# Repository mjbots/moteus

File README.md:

# moteus brushless servo #

This contains full designs for the moteus brushless servo actuator,
including firmware and PCBs.

**WARNING**: This is not just a software project.  It includes designs
for moderately high power electronics.  It has not yet burned down my
(or anyone's that I know of) house, but there are no guarantees.

# Specifications #

| Name                   | r4.11        | r5         | c1         | n1          | x1          |
|------------------------|--------------|------------|------------|-------------|-------------|
| Voltage Input          | 10-44V       | 10-34V     | 10-51V     | 10-54V      | 10-54V      |
| Peak Electrical Power  | 900W @ 30V   | 600W @ 26V | 250W @ 28V | 1.3kW @ 36V | 1kW @ 36V   |
| Mass                   | 14.2g        | 10.0g      | 8.9g       | 14.6g       | 23.8g       |
| Control Rate           | 15-30kHz     | -          | -          | -           | -           |
| PWM Switching Rate     | 15-60kHz     | -          | -          | -           | -           |
| CPU                    | STM32G4      | -          | -          | -           | -           |
| Uncooled phase current | 12A          | 15A        | 5A         | 9A          | 25A         |
| Cooled phase current   | 32A          | 42A        | 14A        | 26A         | 62A         |
| Peak phase current     | 100A         | 100A       | 20A        | 100A        | 120A        |
| Communications         | 5Mbps CAN-FD | -          | -          | -           | -           |
| Dimensions             | 46x53mm      | 40x40x9mm  | 38x38x9mm  | 46x46x8mm   | 56x56x10mm  |

Assembled and tested boards can be purchased at: https://mjbots.com

# Directory structure #

* hw/ - hardware (mechanical and electrical designs)
  * controller/ - PCB design for moteus-r4.11
  * c1/ - PCB design for moteus-c1
  * n1/ - PCB design for moteus-n1
  * x1/ - PCB design for moteus-x1
* fw/ - firmware for brushless controller
* lib/ - client side software
* utils/ - diagnostic tools
* tools/ - bazel build configure
* docs/ - documentation

# Documentation #

* [Quick Start](https://mjbots.github.io/moteus/quick-start)
* [All Documentation](https://mjbots.github.io/moteus/)
* [Discord](https://discord.gg/W4hUpBb)

# Misc #

 * 

# How to support moteus development #

The easiest way to support development the moteus hardware and firmware is as follows:

1) Buy things from https://mjbots.com
2) Build awesome machines!

That's it!  If for some reason you want to go above and beyond, you can sponsor mjbots through github: https://github.com/sponsors/mjbots

# License #

All files contained in this repository, unless otherwise noted, are
available under an Apache 2.0 License:
https://www.apache.org/licenses/LICENSE-2.0

# Trademark #

mjbots Robotic Systems LLC owns and protects the "mjbots" and "moteus" trademarks in many jurisdictions.

If you want to use these names in your project or product, please read the [Trademark Policy](https://mjbots.com/trademark-policy)

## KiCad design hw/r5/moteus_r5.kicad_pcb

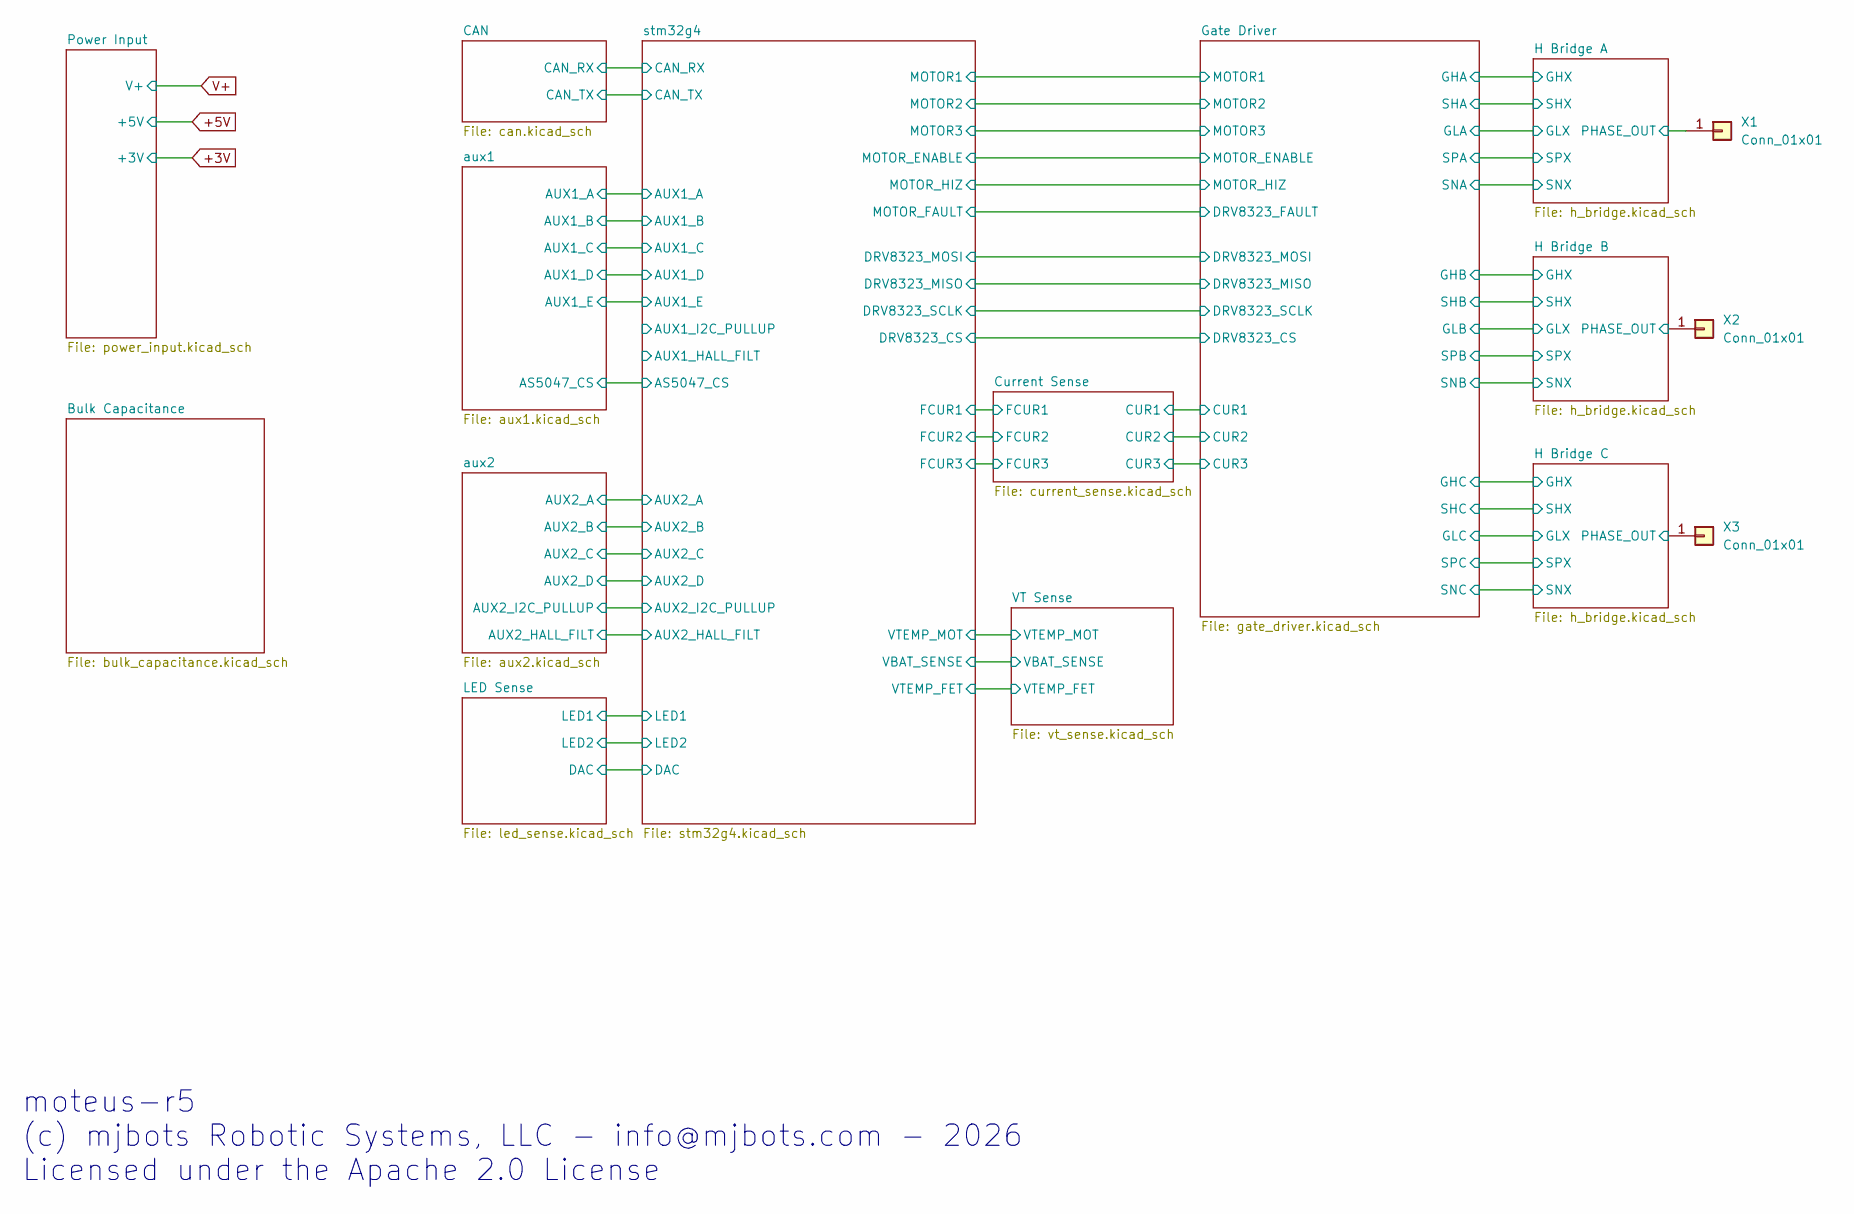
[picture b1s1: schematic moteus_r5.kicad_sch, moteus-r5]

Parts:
X1, X3: Conn_01x01; POWER_M2.5_EDGE
X2: Conn_01x01; POWER_M2.5

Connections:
/H Bridge A/OUTX: X1.1; also elsewhere on the board
/H Bridge B/OUTX: X2.1; also elsewhere on the board
/H Bridge C/OUTX: X3.1; also elsewhere on the board

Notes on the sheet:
moteus-r5 (c) mjbots Robotic Systems, LLC - info@mjbots.com - 2026 Licensed under the Apache 2.0 License

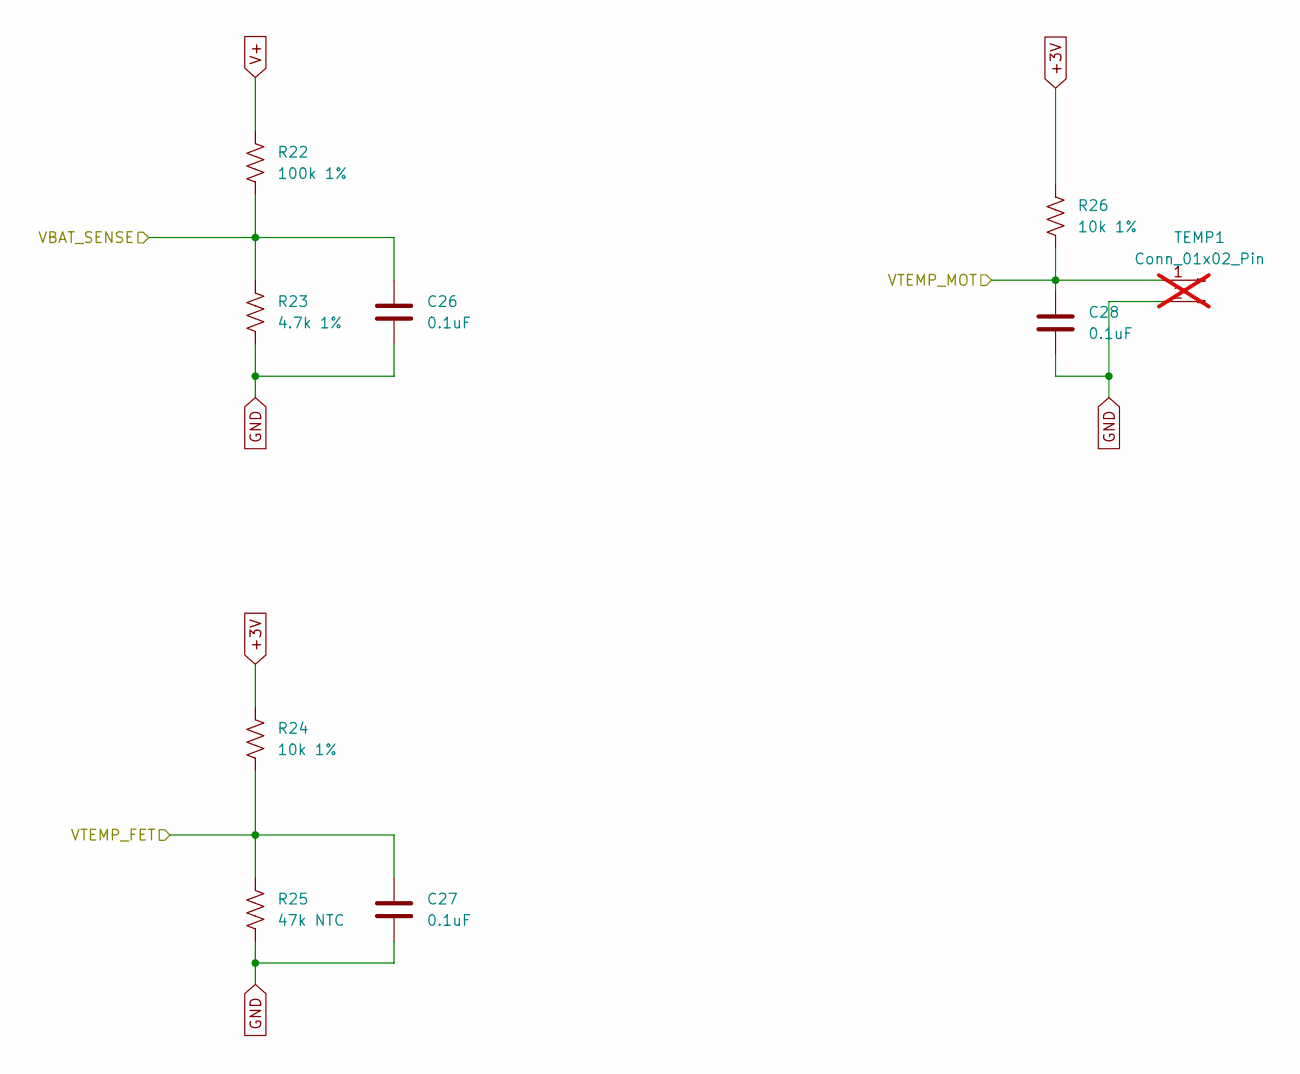
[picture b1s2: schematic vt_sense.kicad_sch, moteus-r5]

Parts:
C26, C27, C28: 0.1uF; C_0402_1005Metric; MPN MF-CAP-0402-0.1uF
R22: 100k 1%; R_0402_1005Metric; MPN RC0402FR-07100KL
R23: 4.7k 1%; R_0402_1005Metric; MPN RC0402FR-074K7L
R24, R26: 10k 1%; R_0402_1005Metric; MPN RC0402FR-0710KL
R25: 47k NTC; R_0402_1005Metric; MPN NCP15WB473F03RC
TEMP1: Conn_01x02_Pin; PinHeader_1x02_P2.00mm_Vertical; not fitted

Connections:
+3V: R24.1, R26.1; also elsewhere on the board
/VT Sense/VBAT_SENSE: C26.1, R22.2, R23.1; also elsewhere on the board
/VT Sense/VTEMP_FET: C27.1, R24.2, R25.1; also elsewhere on the board
/VT Sense/VTEMP_MOT: C28.1, R26.2, TEMP1.1; also elsewhere on the board
GND: C26.2, C27.2, C28.2, R23.2, R25.2, TEMP1.2; also elsewhere on the board
V+: R22.1; also elsewhere on the board

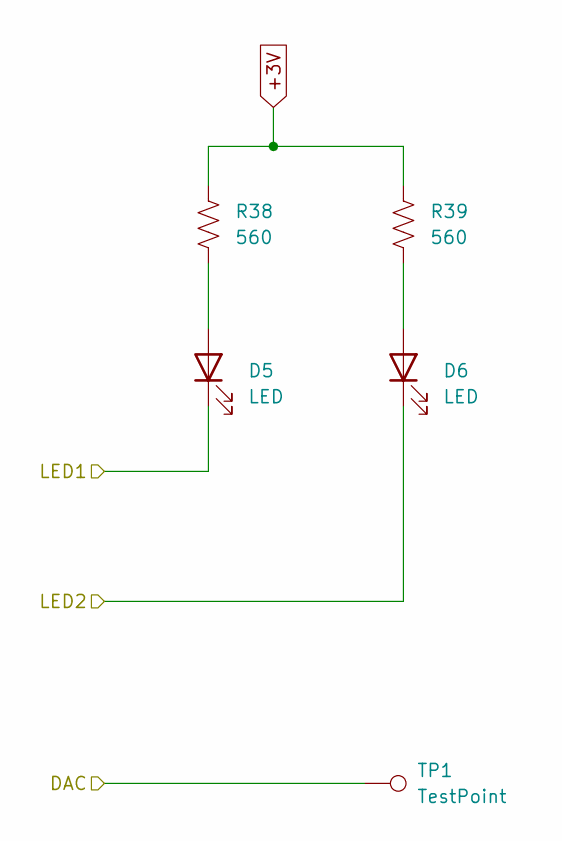
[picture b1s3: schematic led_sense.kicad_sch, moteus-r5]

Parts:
D5: LED; LED_0603_1608Metric; MPN MF-LED-0603-RED
D6: LED; LED_0603_1608Metric; MPN MF-LED-0603-GREEN
R38, R39: 560; R_0402_1005Metric; MPN MF-RES-0402-560
TP1: TestPoint; TestPoint_THTPad_D1.0mm_Drill0.5mm

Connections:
+3V: R38.1, R39.1; also elsewhere on the board
/LED Sense/DAC: TP1.1; also elsewhere on the board
/LED Sense/LED1: D5.1 (K); also elsewhere on the board
/LED Sense/LED2: D6.1 (K); also elsewhere on the board
unnamed: D5.2 (A), R38.2
unnamed: D6.2 (A), R39.2

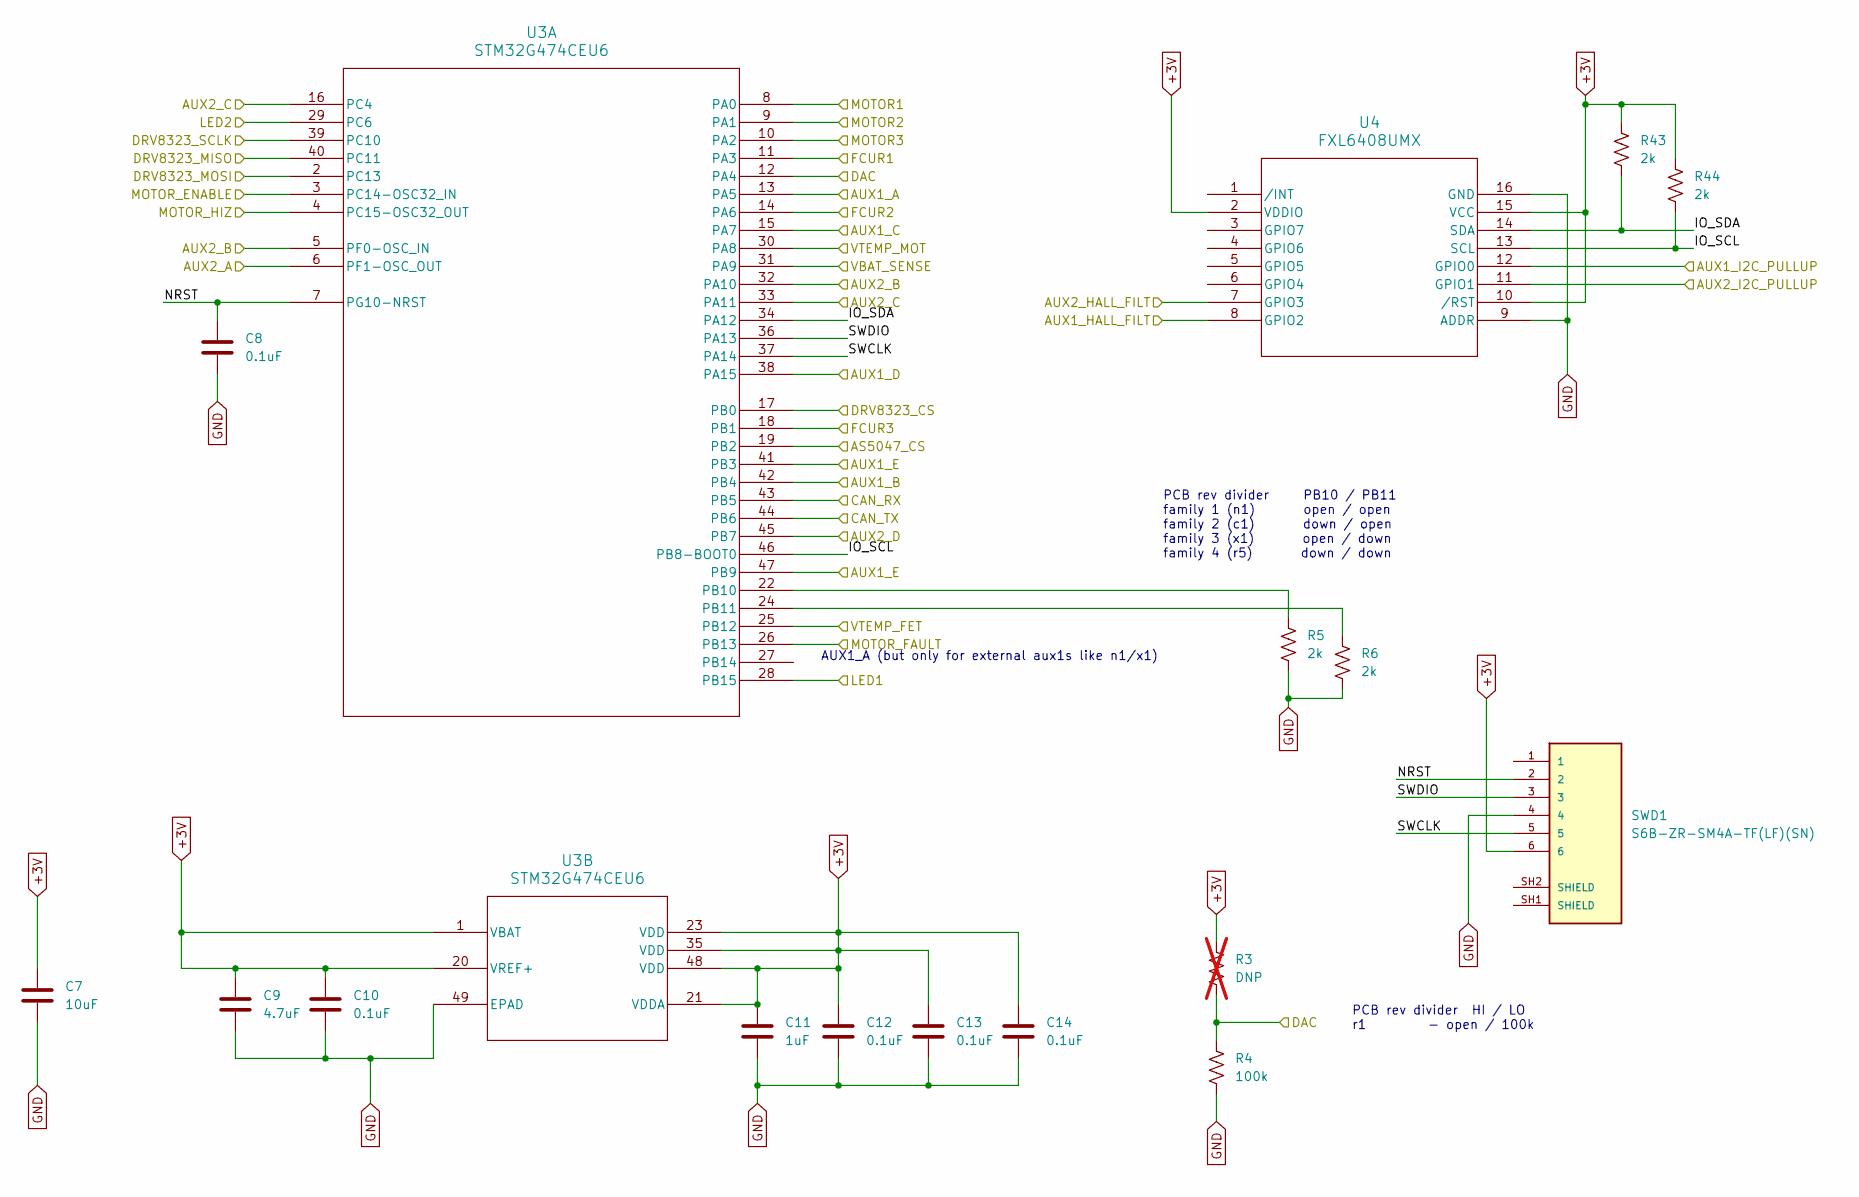
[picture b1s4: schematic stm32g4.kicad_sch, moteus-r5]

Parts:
C7: 10uF; C_1206_3216Metric; MPN MF-CAP-1206-10uF
C8, C10, C12, C13, C14: 0.1uF; C_0402_1005Metric; MPN MF-CAP-0402-0.1uF
C9: 4.7uF; C_0603_1608Metric; MPN CL10A475KP8NNNC
C11: 1uF; C_0402_1005Metric; MPN MF-CAP-0402-1uF
R3: DNP; R_0402_1005Metric; not fitted
R4: 100k; R_0402_1005Metric; MPN RC0402FR-07100KL
R5, R6, R43, R44: 2k; R_0402_1005Metric; MPN MF-RES-0402-2K
SWD1: S6B-ZR-SM4A-TF(LF)(SN); JST_S6B-ZR-SM4A-TF(LF)(SN); MPN S6B-ZR-SM4A-TF(LF)(SN)
U3: STM32G474CEU6; UFQFPN-48_7X7X0P55MM; MPN STM32G474CEU6
U4: FXL6408UMX; UMLP16_1P8X2P6_ONS; MPN FXL6408UMX

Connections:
+3V: C7.1, C9.1, C10.1, C11.1, C12.1, C13.1, C14.1, R3.1, R43.1, R44.1, SWD1.6, U3.1 (VBAT), U3.20 (VREF+), U3.21 (VDDA), U3.23 (VDD), U3.35 (VDD), U3.48 (VDD), U4.2 (VDDIO), U4.10 (/RST), U4.15 (VCC); also elsewhere on the board
/CAN/CAN_RX: U3.43 (PB5); also elsewhere on the board
/CAN/CAN_TX: U3.44 (PB6); also elsewhere on the board
/Current Sense/FCUR1: U3.11 (PA3); also elsewhere on the board
/Current Sense/FCUR2: U3.14 (PA6); also elsewhere on the board
/Current Sense/FCUR3: U3.18 (PB1); also elsewhere on the board
/Gate Driver/DRV8323_CS: U3.17 (PB0); also elsewhere on the board
/Gate Driver/DRV8323_FAULT: U3.26 (PB13); also elsewhere on the board
/Gate Driver/DRV8323_MISO: U3.40 (PC11); also elsewhere on the board
/Gate Driver/DRV8323_MOSI: U3.2 (PC13); also elsewhere on the board
/Gate Driver/DRV8323_SCLK: U3.39 (PC10); also elsewhere on the board
/Gate Driver/MOTOR1: U3.8 (PA0); also elsewhere on the board
/Gate Driver/MOTOR2: U3.9 (PA1); also elsewhere on the board
/Gate Driver/MOTOR3: U3.10 (PA2); also elsewhere on the board
/Gate Driver/MOTOR_ENABLE: U3.3 (PC14-OSC32_IN); also elsewhere on the board
/Gate Driver/MOTOR_HIZ: U3.4 (PC15-OSC32_OUT); also elsewhere on the board
/LED Sense/DAC: R3.2, R4.1, U3.12 (PA4); also elsewhere on the board
/LED Sense/LED1: U3.28 (PB15); also elsewhere on the board
/LED Sense/LED2: U3.29 (PC6); also elsewhere on the board
/VT Sense/VBAT_SENSE: U3.31 (PA9); also elsewhere on the board
/VT Sense/VTEMP_FET: U3.25 (PB12); also elsewhere on the board
/VT Sense/VTEMP_MOT: U3.30 (PA8); also elsewhere on the board
/aux1/AS5047_CS: U3.19 (PB2); also elsewhere on the board
/aux1/AUX1_A: U3.13 (PA5); also elsewhere on the board
/aux1/AUX1_B: U3.42 (PB4); also elsewhere on the board
/aux1/AUX1_C: U3.15 (PA7); also elsewhere on the board
/aux1/AUX1_D: U3.38 (PA15); also elsewhere on the board
/aux1/AUX1_E: U3.41 (PB3), U3.47 (PB9); also elsewhere on the board
/aux2/AUX2_A: U3.6 (PF1-OSC_OUT); also elsewhere on the board
/aux2/AUX2_B: U3.5 (PF0-OSC_IN), U3.32 (PA10); also elsewhere on the board
/aux2/AUX2_C: U3.16 (PC4), U3.33 (PA11); also elsewhere on the board
/aux2/AUX2_D: U3.45 (PB7); also elsewhere on the board
/aux2/AUX2_HALL_FILT: U4.7 (GPIO3); also elsewhere on the board
/aux2/AUX2_I2C_PULLUP: U4.11 (GPIO1); also elsewhere on the board
/stm32g4/AUX1_HALL_FILT: U4.8 (GPIO2)
/stm32g4/AUX1_I2C_PULLUP: U4.12 (GPIO0)
/stm32g4/IO_SCL: R44.2, U3.46 (PB8-BOOT0), U4.13 (SCL)
/stm32g4/IO_SDA: R43.2, U3.34 (PA12), U4.14 (SDA)
/stm32g4/NRST: C8.1, SWD1.2, U3.7 (PG10-NRST)
/stm32g4/SWCLK: SWD1.5, U3.37 (PA14)
/stm32g4/SWDIO: SWD1.3, U3.36 (PA13)
GND: C7.2, C8.2, C9.2, C10.2, C11.2, C12.2, C13.2, C14.2, R4.2, R5.2, R6.2, SWD1.4, U3.49 (EPAD), U4.9 (ADDR), U4.16 (GND); also elsewhere on the board
unnamed: R5.1, U3.22 (PB10)
unnamed: R6.1, U3.24 (PB11)

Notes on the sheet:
PCB rev divider HI / LO r1 - open / 100k
AUX1_A (but only for external aux1s like n1/x1)
PCB rev divider PB10 / PB11 family 1 (n1) open / open family 2 (c1) down / open family 3 (x1) open / down family 4 (r5) down / down

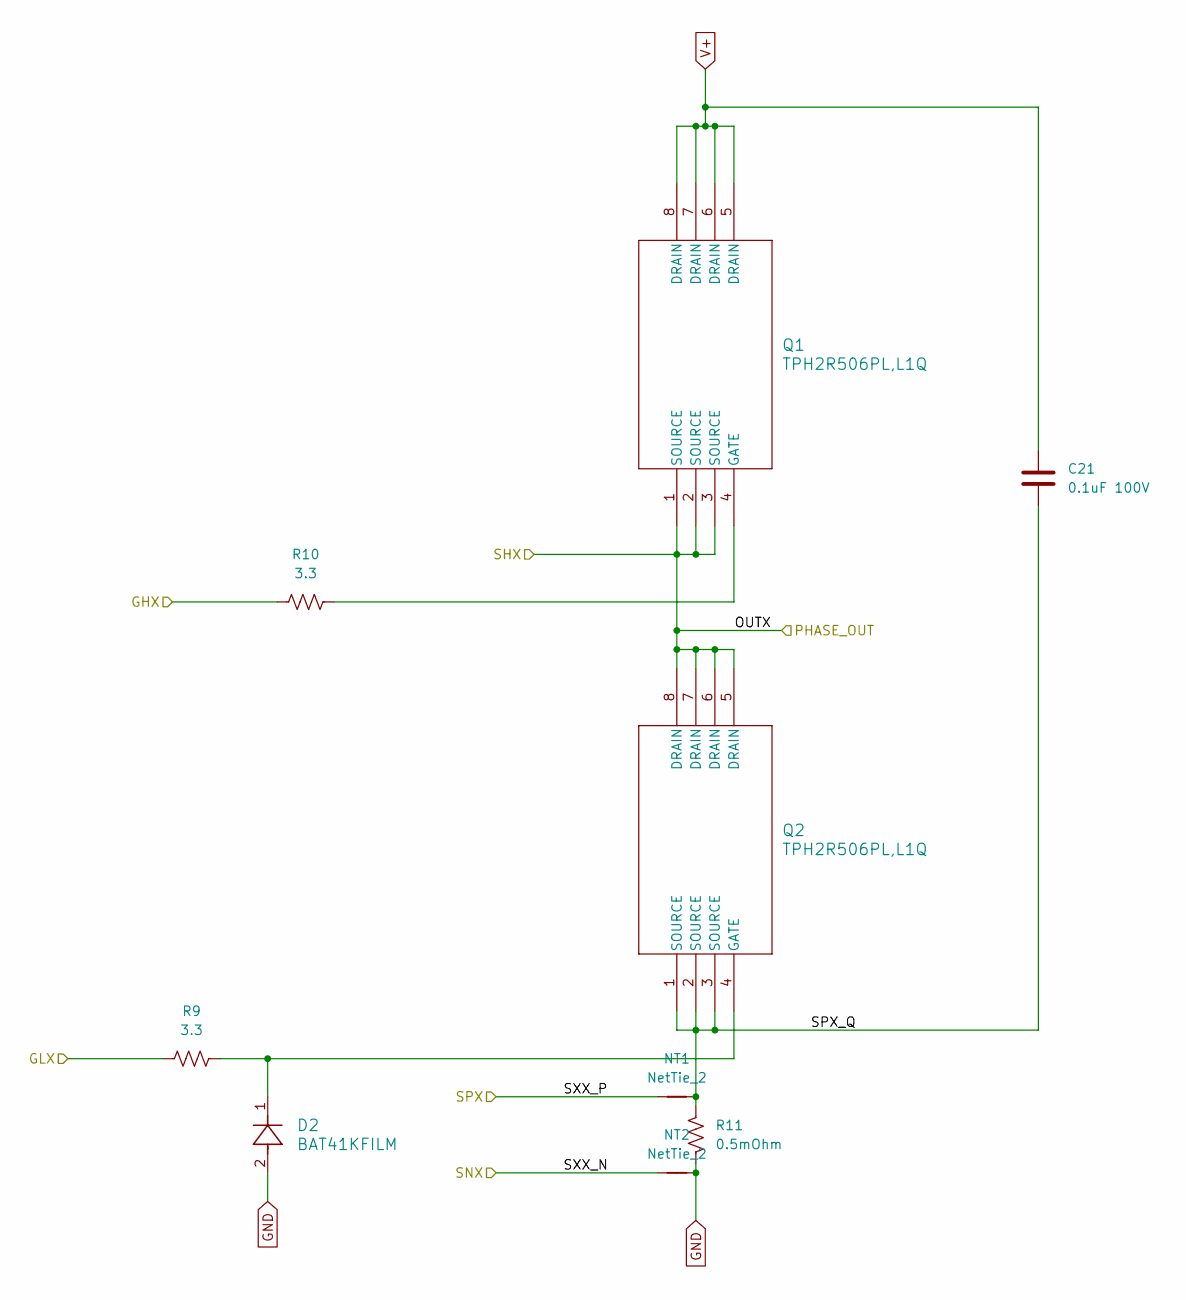
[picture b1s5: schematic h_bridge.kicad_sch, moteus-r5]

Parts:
C21: 0.1uF 100V; C_1206_3216Metric; MPN KGM31DR72A104KL
D2: BAT41KFILM; SOD-523_STM; MPN BAT41KFILM
NT1, NT2: NetTie_2; NetTie-2_SMD_Pad0.2
Q1, Q2: TPH2R506PL,L1Q; TPCA8120; MPN TPH2R506PL,L1Q
R9, R10: 3.3; R_0603_1608Metric; MPN ERJ-3RQF3R3V
R11: 0.5mOhm; R_1206_3216Metric; MPN HCS1206FTL500

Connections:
/Gate Driver/GHA: R10.1; also elsewhere on the board
/Gate Driver/GLA: R9.1; also elsewhere on the board
/H Bridge A/OUTX: Q1.1 (SOURCE), Q1.2 (SOURCE), Q1.3 (SOURCE), Q2.5 (DRAIN), Q2.6 (DRAIN), Q2.7 (DRAIN), Q2.8 (DRAIN); also elsewhere on the board
/H Bridge A/SPX_Q: C21.2, NT1.2, Q2.1 (SOURCE), Q2.2 (SOURCE), Q2.3 (SOURCE), R11.1
/H Bridge A/SXX_N: NT2.1; also elsewhere on the board
/H Bridge A/SXX_P: NT1.1; also elsewhere on the board
GND: D2.2, NT2.2, R11.2; also elsewhere on the board
unnamed: Q1.4 (GATE), R10.2
unnamed: D2.1, Q2.4 (GATE), R9.2
V+: C21.1, Q1.5 (DRAIN), Q1.6 (DRAIN), Q1.7 (DRAIN), Q1.8 (DRAIN); also elsewhere on the board

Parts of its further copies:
C22, C23: 0.1uF 100V; C_1206_3216Metric; MPN KGM31DR72A104KL
D3, D4: BAT41KFILM; SOD-523_STM; MPN BAT41KFILM
NT3, NT4, NT5, NT6: NetTie_2; NetTie-2_SMD_Pad0.2
Q3, Q4, Q5, Q6: TPH2R506PL,L1Q; TPCA8120; MPN TPH2R506PL,L1Q
R12, R13, R15, R16: 3.3; R_0603_1608Metric; MPN ERJ-3RQF3R3V
R14, R17: 0.5mOhm; R_1206_3216Metric; MPN HCS1206FTL500

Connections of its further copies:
/Gate Driver/GHB: R13.1; also elsewhere on the board
/Gate Driver/GHC: R16.1; also elsewhere on the board
/Gate Driver/GLB: R12.1; also elsewhere on the board
/Gate Driver/GLC: R15.1; also elsewhere on the board
/H Bridge B/OUTX: Q3.1 (SOURCE), Q3.2 (SOURCE), Q3.3 (SOURCE), Q4.5 (DRAIN), Q4.6 (DRAIN), Q4.7 (DRAIN), Q4.8 (DRAIN); also elsewhere on the board
/H Bridge B/SPX_Q: C22.2, NT3.2, Q4.1 (SOURCE), Q4.2 (SOURCE), Q4.3 (SOURCE), R14.1
/H Bridge B/SXX_N: NT4.1; also elsewhere on the board
/H Bridge B/SXX_P: NT3.1; also elsewhere on the board
/H Bridge C/OUTX: Q5.1 (SOURCE), Q5.2 (SOURCE), Q5.3 (SOURCE), Q6.5 (DRAIN), Q6.6 (DRAIN), Q6.7 (DRAIN), Q6.8 (DRAIN); also elsewhere on the board
/H Bridge C/SPX_Q: C23.2, NT5.2, Q6.1 (SOURCE), Q6.2 (SOURCE), Q6.3 (SOURCE), R17.1
/H Bridge C/SXX_N: NT6.1; also elsewhere on the board
/H Bridge C/SXX_P: NT5.1; also elsewhere on the board
GND: D3.2, D4.2, NT4.2, NT6.2, R14.2, R17.2; also elsewhere on the board
unnamed: Q3.4 (GATE), R13.2
unnamed: D3.1, Q4.4 (GATE), R12.2
unnamed: Q5.4 (GATE), R16.2
unnamed: D4.1, Q6.4 (GATE), R15.2
V+: C22.1, C23.1, Q3.5 (DRAIN), Q3.6 (DRAIN), Q3.7 (DRAIN), Q3.8 (DRAIN), Q5.5 (DRAIN), Q5.6 (DRAIN), Q5.7 (DRAIN), Q5.8 (DRAIN); also elsewhere on the board

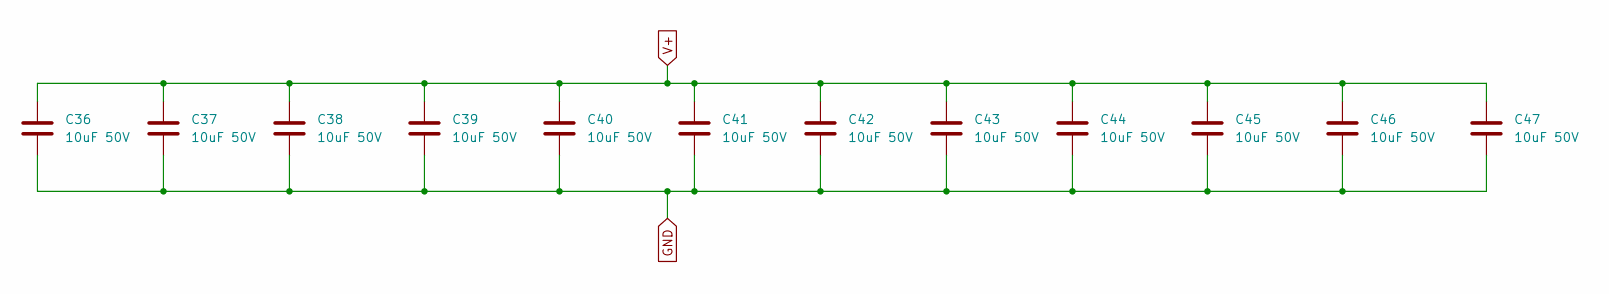
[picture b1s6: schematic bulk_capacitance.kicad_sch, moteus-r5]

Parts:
C36, C37, C38, C39, C40, C41, C42, C43, C44, C45, C46, C47: 10uF 50V; C_1206_3216Metric; MPN CGA5L1X7R1H106K160AE

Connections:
GND: C36.2, C37.2, C38.2, C39.2, C40.2, C41.2, C42.2, C43.2, C44.2, C45.2, C46.2, C47.2; also elsewhere on the board
V+: C36.1, C37.1, C38.1, C39.1, C40.1, C41.1, C42.1, C43.1, C44.1, C45.1, C46.1, C47.1; also elsewhere on the board

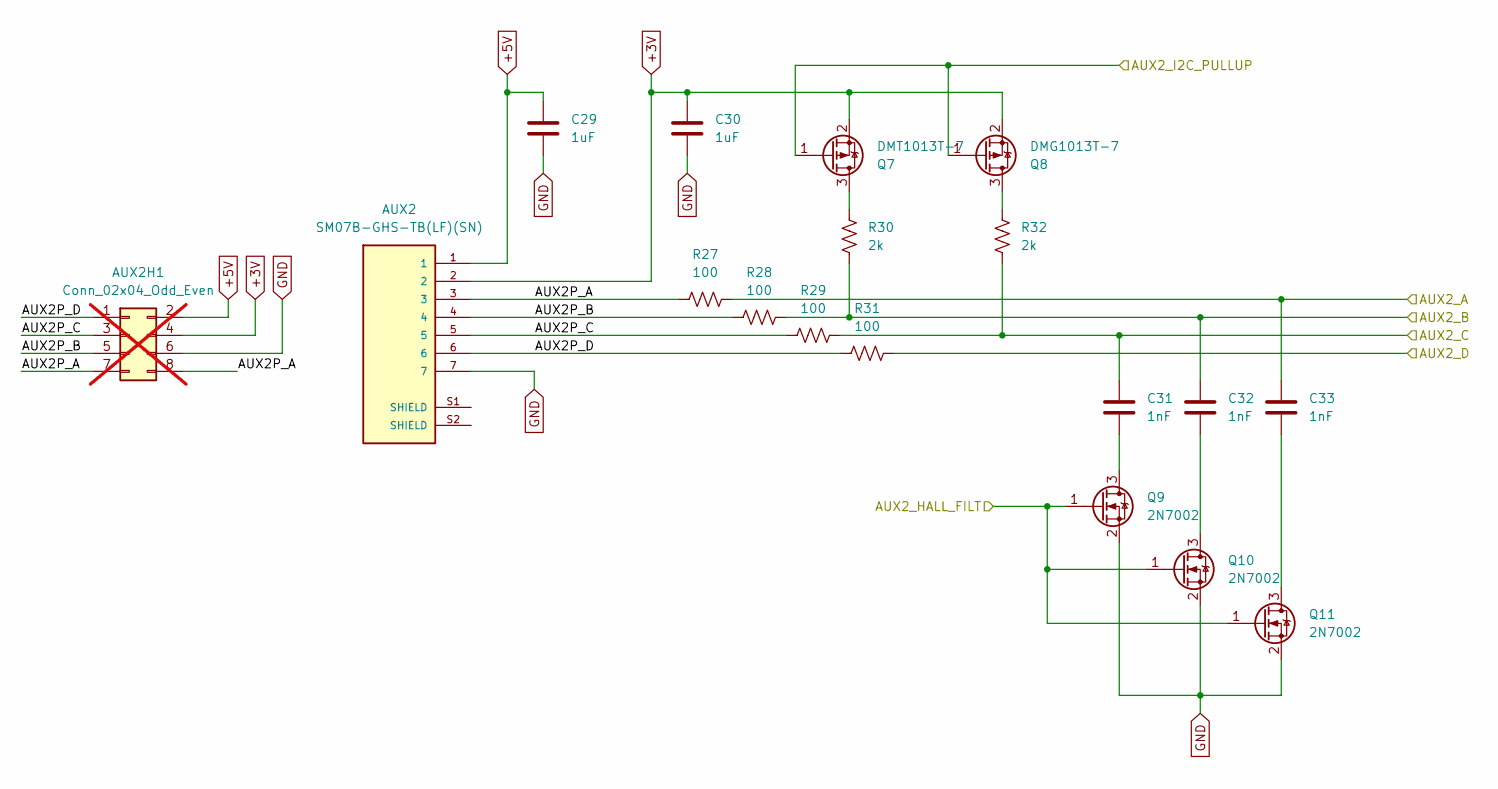
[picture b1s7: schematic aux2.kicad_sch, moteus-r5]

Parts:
AUX2: SM07B-GHS-TB(LF)(SN); JST_SM07B-GHS-TB(LF)(SN); MPN SM07B-GHS-TB(LF)(SN)
AUX2H1: Conn_02x04_Odd_Even; PinHeader_2x04_P1.27mm_Vertical; not fitted
C29, C30: 1uF; C_0402_1005Metric; MPN MF-CAP-0402-1uF
C31, C32, C33: 1nF; C_0402_1005Metric; MPN MF-CAP-0402-1nF
Q7: DMT1013T-7; SOT-523; MPN DMG1013T-7
Q8: DMG1013T-7; SOT-523; MPN DMG1013T-7
Q9, Q10, Q11: 2N7002; SOT-523; MPN 2N7002KTB_R1_00001
R27, R28, R29, R31: 100; R_0402_1005Metric; MPN MF-RES-0402-100
R30, R32: 2k; R_0402_1005Metric; MPN MF-RES-0402-2K

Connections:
+3V: AUX2.2, AUX2H1.4, C30.1, Q7.2 (S), Q8.2 (S); also elsewhere on the board
+5V: AUX2.1, AUX2H1.2, C29.1; also elsewhere on the board
/aux2/AUX2P_A: AUX2.3, AUX2H1.7, AUX2H1.8, R27.1
/aux2/AUX2P_B: AUX2.4, AUX2H1.5, R28.1
/aux2/AUX2P_C: AUX2.5, AUX2H1.3, R29.1
/aux2/AUX2P_D: AUX2.6, AUX2H1.1, R31.1
/aux2/AUX2_A: C33.1, R27.2; also elsewhere on the board
/aux2/AUX2_B: C32.1, R28.2, R30.2; also elsewhere on the board
/aux2/AUX2_C: C31.1, R29.2, R32.2; also elsewhere on the board
/aux2/AUX2_D: R31.2; also elsewhere on the board
/aux2/AUX2_HALL_FILT: Q9.1 (G), Q10.1 (G), Q11.1 (G); also elsewhere on the board
/aux2/AUX2_I2C_PULLUP: Q7.1 (G), Q8.1 (G); also elsewhere on the board
GND: AUX2.7, AUX2H1.6, C29.2, C30.2, Q9.2 (S), Q10.2 (S), Q11.2 (S); also elsewhere on the board
unnamed: Q7.3 (D), R30.1
unnamed: Q8.3 (D), R32.1
unnamed: C31.2, Q9.3 (D)
unnamed: C32.2, Q10.3 (D)
unnamed: C33.2, Q11.3 (D)

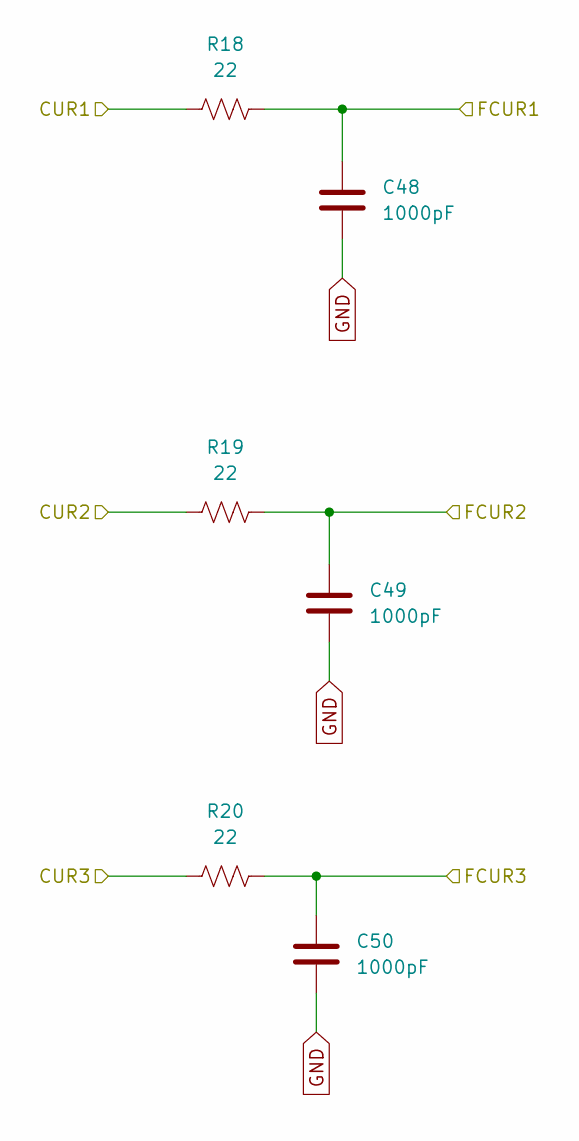
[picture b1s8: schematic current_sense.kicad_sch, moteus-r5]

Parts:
C48, C49: 1000pF; C_0402_1005Metric; MPN MF-CAP-0402-1nF
C50: 1000pF; C_0603_1608Metric; MPN MF-CAP-0603-1nF
R18, R19, R20: 22; R_0402_1005Metric; MPN MF-RES-0402-22

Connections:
/Current Sense/CUR1: R18.1; also elsewhere on the board
/Current Sense/CUR2: R19.1; also elsewhere on the board
/Current Sense/CUR3: R20.1; also elsewhere on the board
/Current Sense/FCUR1: C48.1, R18.2; also elsewhere on the board
/Current Sense/FCUR2: C49.1, R19.2; also elsewhere on the board
/Current Sense/FCUR3: C50.1, R20.2; also elsewhere on the board
GND: C48.2, C49.2, C50.2; also elsewhere on the board

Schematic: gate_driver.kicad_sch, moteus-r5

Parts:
C15: 1uF; C_0603_1608Metric; MPN MF-CAP-0603-1uF
C16: 0.1uF 100V; C_0603_1608Metric; MPN GCJ188R72A104KA01D
C17: 1uF; C_0402_1005Metric; MPN MF-CAP-0402-1uF
C18: 1uF 25V; C_0603_1608Metric; MPN C1608X7R1E105K080AE
C19: 47nF 100V; C_0603_1608Metric; MPN C0603X473K1RAC7867
C20: 1uF; C_0603_1608Metric; MPN C1608X7R1E105K080AE
R7, R8: 2k; R_0402_1005Metric; MPN MF-RES-0402-2K
U5: DRV8353SRTAR; RTA0040B; MPN DRV8353SRTAR

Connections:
+3V: C15.2, R7.1, R8.1, U5.24 (VREF); also elsewhere on the board
/Current Sense/CUR1: U5.21 (SOC); also elsewhere on the board
/Current Sense/CUR2: U5.22 (SOB); also elsewhere on the board
/Current Sense/CUR3: U5.23 (SOA); also elsewhere on the board
/Gate Driver/CPH: C19.2, U5.2 (CPH)
/Gate Driver/CPL: C19.1, U5.1 (CPL)
/Gate Driver/DRV8323_CS: U5.30 (SCS_N); also elsewhere on the board
/Gate Driver/DRV8323_FAULT: R8.2, U5.26 (FAULT_N); also elsewhere on the board
/Gate Driver/DRV8323_MISO: R7.2, U5.27 (SDO); also elsewhere on the board
/Gate Driver/DRV8323_MOSI: U5.28 (SDI); also elsewhere on the board
/Gate Driver/DRV8323_SCLK: U5.29 (SCLK); also elsewhere on the board
/Gate Driver/GHA: U5.6 (GHA); also elsewhere on the board
/Gate Driver/GHB: U5.15 (GHB); also elsewhere on the board
/Gate Driver/GHC: U5.16 (GHC); also elsewhere on the board
/Gate Driver/GLA: U5.8 (GLA); also elsewhere on the board
/Gate Driver/GLB: U5.13 (GLB); also elsewhere on the board
/Gate Driver/GLC: U5.18 (GLC); also elsewhere on the board
/Gate Driver/MOTOR1: U5.32 (INHA); also elsewhere on the board
/Gate Driver/MOTOR2: U5.34 (INHB); also elsewhere on the board
/Gate Driver/MOTOR3: U5.36 (INHC); also elsewhere on the board
/Gate Driver/MOTOR_ENABLE: U5.31 (ENABLE); also elsewhere on the board
/Gate Driver/MOTOR_HIZ: U5.33 (INLA), U5.35 (INLB), U5.37 (INLC); also elsewhere on the board
/Gate Driver/VCP: C18.2, U5.5 (VCP)
/H Bridge A/OUTX: U5.7 (SHA); also elsewhere on the board
/H Bridge A/SXX_N: U5.10 (SNA); also elsewhere on the board
/H Bridge A/SXX_P: U5.9 (SPA); also elsewhere on the board
/H Bridge B/OUTX: U5.14 (SHB); also elsewhere on the board
/H Bridge B/SXX_N: U5.11 (SNB); also elsewhere on the board
/H Bridge B/SXX_P: U5.12 (SPB); also elsewhere on the board
/H Bridge C/OUTX: U5.17 (SHC); also elsewhere on the board
/H Bridge C/SXX_N: U5.20 (SNC); also elsewhere on the board
/H Bridge C/SXX_P: U5.19 (SPC); also elsewhere on the board
GND: C15.1, C16.1, C17.1, C20.1, U5.25 (AGND), U5.39 (PGND), U5.41 (PAD); also elsewhere on the board
unnamed: C17.2, U5.38 (DVDD)
unnamed: C20.2, U5.40 (VGLS)
V+: C16.2, C18.1, U5.3 (VM), U5.4 (VDRAIN); also elsewhere on the board

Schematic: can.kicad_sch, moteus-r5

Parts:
C24, C25: 0.1uF; C_0402_1005Metric; MPN MF-CAP-0402-0.1uF
CAN1: S3B-PH-SM4-TB(LF)(SN); JST_S3B-PH-SM4-TB(LF)(SN); MPN S3B-PH-SM4-TB(LF)(SN)
CAN_DBG1: Conn_01x03_Pin; PinHeader_1x03_P2.00mm_Vertical; not fitted
R21: 120; R_0603_1608Metric; MPN RC0805FR-07120RL; not fitted
U6: TCAN1057AEV-Q1; SOIC-8_3.9x4.9mm_P1.27mm; MPN TCAN1057AEVDRQ1

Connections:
+3V: C24.1, U6.5 (VIO); also elsewhere on the board
+5V: C25.1, U6.3 (VCC); also elsewhere on the board
/CAN/CAN_N: CAN1.2, CAN_DBG1.2, R21.2, U6.6 (CANL)
/CAN/CAN_P: CAN1.1, CAN_DBG1.1, R21.1, U6.7 (CANH)
/CAN/CAN_RX: U6.4 (RXD); also elsewhere on the board
/CAN/CAN_TX: U6.1 (TXD); also elsewhere on the board
GND: C24.2, C25.2, CAN1.3, CAN_DBG1.3, U6.2 (GND), U6.8 (STB), U6.9 (PAD); also elsewhere on the board

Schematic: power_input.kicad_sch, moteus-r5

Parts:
C1: 1uF 100V; C_0805_2012Metric; MPN GCM21BC72A105KE36L
C2: 1uF; C_0603_1608Metric; MPN MF-CAP-0603-1uF
C4: 22uF; C_1206_3216Metric; MPN GRM31CR71A226KE15L
C5, C6: 1uF; C_0402_1005Metric; MPN MF-CAP-0402-1uF
D1: SMBJ33D-M3/I; D_SMB; MPN SMBJ33D-M3/I
H1, H2, H3, H4: MountingHole_Pad; M3_MOUNT_CORNER
J1: XT30PW-M; AMASS_XT30PW-M; MPN XT30PW-M
L1: 47uH; IND_4018-WE-LQS_WRE; MPN SRN4018-470M
R1, R40, R41, R42: DNP; R_0402_1005Metric; not fitted
R2: 0; R_0402_1005Metric; MPN MF-RES-0402-0
U1: MAX15062BATA+T; 21-0487A_MXM; MPN MAX15062BATA+T
U2: TLV70233PDBVR; SOT-23-5; MPN TLV70233PDBVR
VN1: Conn_01x01; POWER_M2.5
VP1: Conn_01x01; POWER_M2.5

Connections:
+3V: C6.1, U2.5 (OUT); also elsewhere on the board
+5V: C4.1, C5.1, L1.1, U1.4 (FB/VOUT), U2.1 (IN), U2.3 (EN); also elsewhere on the board
/Power Input/LX: L1.2, U1.8 (LX)
GND: C1.2, C2.2, C4.2, C5.2, C6.2, D1.2 (A2), J1.N, R1.2, R2.2, R40.2, R41.2, R42.2, U1.7 (GND), U2.2 (GND), VN1.1; also elsewhere on the board
MOUNT_GND1: H1.1, R1.1
MOUNT_GND2: H2.1, R40.1
MOUNT_GND3: H3.1, R41.1
MOUNT_GND4: H4.1, R42.1
unnamed: R2.1, U1.5 (MODE)
unnamed: C2.1, U1.3 (VCC)
V+: C1.1, D1.1 (A1), J1.P, U1.1 (VIN), U1.2 (EN/UVLO), VP1.1; also elsewhere on the board

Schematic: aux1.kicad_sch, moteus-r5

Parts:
AUX1: Conn_01x04; PinHeader_2x02_P1.27mm_Vertical; not fitted
C34: 1uF; C_0402_1005Metric; MPN MF-CAP-0402-1uF
C35: 0.1uF; C_0402_1005Metric; MPN MF-CAP-0402-0.1uF
R33, R35: 0; R_0402_1005Metric; MPN MF-RES-0402-0
R34: 0; R_0603_1608Metric; MPN MF-RES-0603-0
R36, R37: 100; R_0402_1005Metric; MPN MF-RES-0402-100
U7: MA600; QFN-16-1EP_3x3mm_P0.5mm_EP1.75x1.75mm; MPN MA600GQE-0000

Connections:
+3V: AUX1.1, C34.1, C35.1, U7.13 (VDD), U7.14 (AVDD); also elsewhere on the board
/aux1/AS5047_CS: U7.5 (~CS); also elsewhere on the board
/aux1/AUX1P_D: AUX1.2, R36.1
/aux1/AUX1P_E: AUX1.3, R37.1
/aux1/AUX1_A: R34.1; also elsewhere on the board
/aux1/AUX1_B: U7.7 (MISO); also elsewhere on the board
/aux1/AUX1_C: R33.1; also elsewhere on the board
/aux1/AUX1_D: R36.2; also elsewhere on the board
/aux1/AUX1_E: R37.2; also elsewhere on the board
GND: AUX1.4, C34.2, C35.2, R35.1; also elsewhere on the board
unnamed: R35.2, U7.8 (GND), U7.10 (TEST)
unnamed: R33.2, U7.4 (MOSI)
unnamed: R34.2, U7.12 (SCLK)

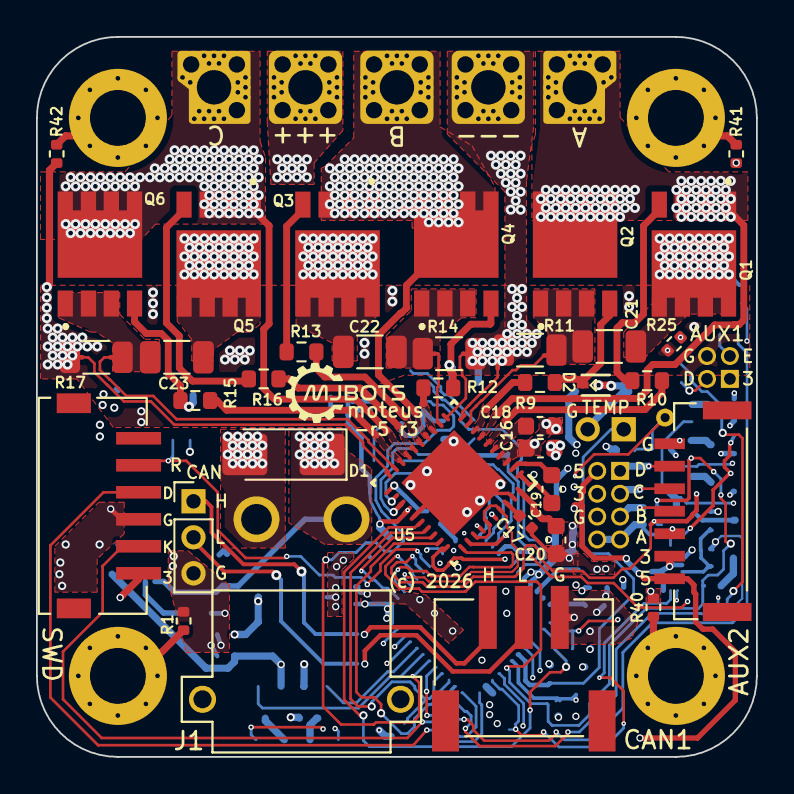
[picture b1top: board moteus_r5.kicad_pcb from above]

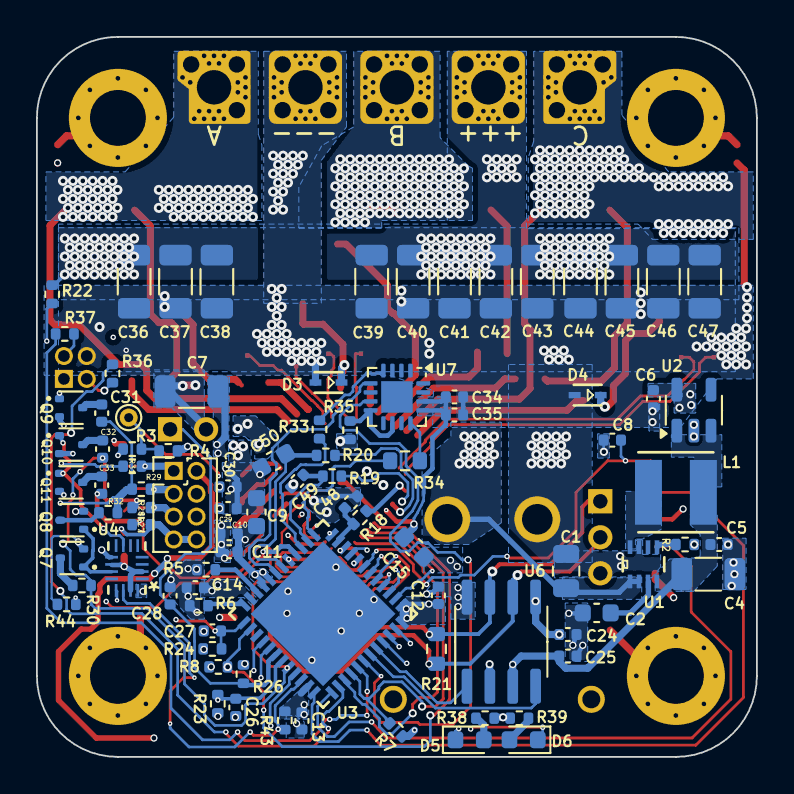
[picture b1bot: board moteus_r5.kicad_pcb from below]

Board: 4 copper layers, 40.0 x 40.0 mm, 142 parts (90 on the bottom side), 101 nets.

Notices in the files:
hw/c1/r1.2/moteus_c1.kicad_pcb:
(c) 2024
hw/mjuart/mjuart.kicad_pcb:
mjuart r1 (c) 2026
hw/r5/moteus_r5.kicad_pcb:
(c) 2026
